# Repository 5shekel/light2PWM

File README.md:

# light 2 PWM
light controlled dimmer circuit that used pulse width modulation (PWM) to drive LEDs  
by STEPHEN HOBLEY [[1]](http://www.stephenhobley.com/blog/2010/09/17/light-controlled-pwm-generator/)

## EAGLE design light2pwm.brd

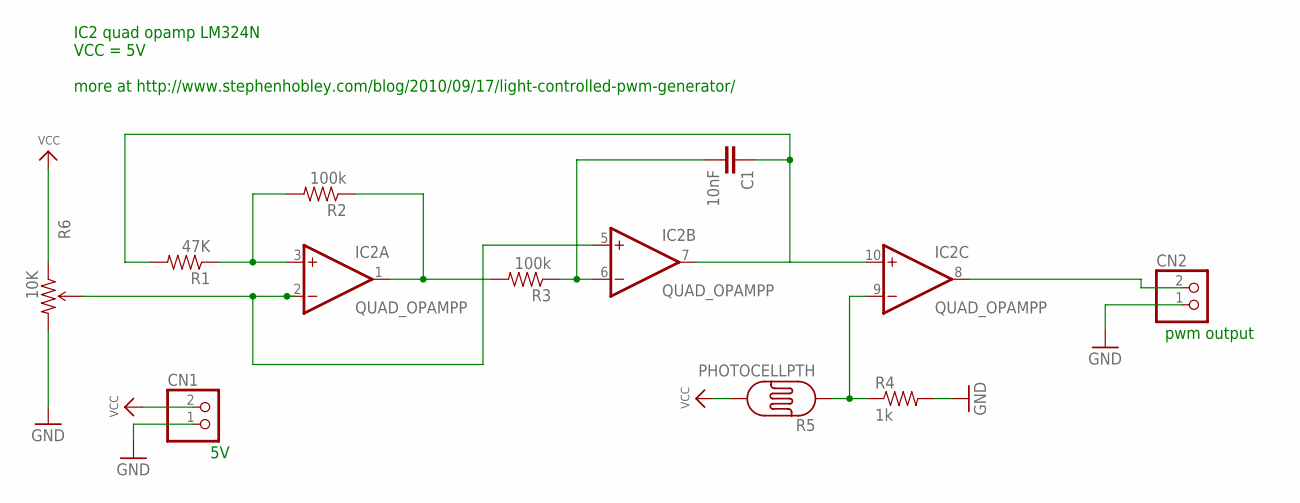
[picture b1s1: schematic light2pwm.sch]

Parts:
C1: 10nF; 0402-CAP
CN1, CN2: JST_2PIN-THM; JST-PH-2-THM
IC2: QUAD_OPAMPP; DIL14
R1: 47K; AXIAL-0.3EZ
R2, R3: 100k; AXIAL-0.3EZ
R4: 1k; AXIAL-0.3EZ
R5: PHOTOCELLPTH; PHOTOCELL
R6: 10K; 3386U

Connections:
GND: CN1.1 (2), CN2.1 (2), R4.P$2 (2), R6.3 (CW)
unnamed: IC2.3 (+IN), R1.P$1 (1), R2.P$2 (2)
unnamed: C1.1, IC2.7 (OUT), IC2.10 (+IN), R1.P$2 (2)
unnamed: IC2.1 (OUT), R2.P$1 (1), R3.P$2 (2)
unnamed: IC2.2 (-IN), IC2.5 (+IN), R6.2 (WIPER)
unnamed: C1.2, IC2.6 (-IN), R3.P$1 (1)
unnamed: CN2.2 (1), IC2.8 (OUT)
unnamed: IC2.9 (-IN), R4.P$1 (1), R5.1
V+: IC2.4 (V+)
V-: IC2.11 (V-)
VCC: CN1.2 (1), R5.2, R6.1 (CCW)

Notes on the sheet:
IC2 quad opamp LM324N VCC = 5V more at http://www.stephenhobley.com/blog/2010/09/17/light-controlled-pwm-generator/
pwm output

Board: 2 copper layers, 10 parts (0 on the bottom side), 9 nets, no tracks yet.

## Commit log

2015-06-02 inital commit, schema is ready
2015-06-02 pwm output pin added, next add transistor
2015-06-02 add ignore

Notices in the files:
parts and their libraries:
SparkFun-Retired: Licensing:Creative Commons ShareAlike 4.0 International - https://creativecommons.org/licenses/by-sa/4.0
microbuilder: This work is placed in the public domain, and may be freely used for commercial and non-commercial work with the following conditions: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
